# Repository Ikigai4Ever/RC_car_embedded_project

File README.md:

# RC_car_embedded_project

## PCB Portion 

- [NUCLEO-L476RG Footprints](https://www.snapeda.com/parts/NUCLEO-L476RG/STMicroelectronics/view-part/)
- [HC-05 Data Sheet](https://engineering.purdue.edu/477grp14/Team/journal/img%20-%20member3/documents/HC05.pdf)
- [Joystick Data Sheet](https://naylampmechatronics.com/img/cms/Datasheets/000036%20-%20datasheet%20KY-023-Joy-IT.pdf)

---

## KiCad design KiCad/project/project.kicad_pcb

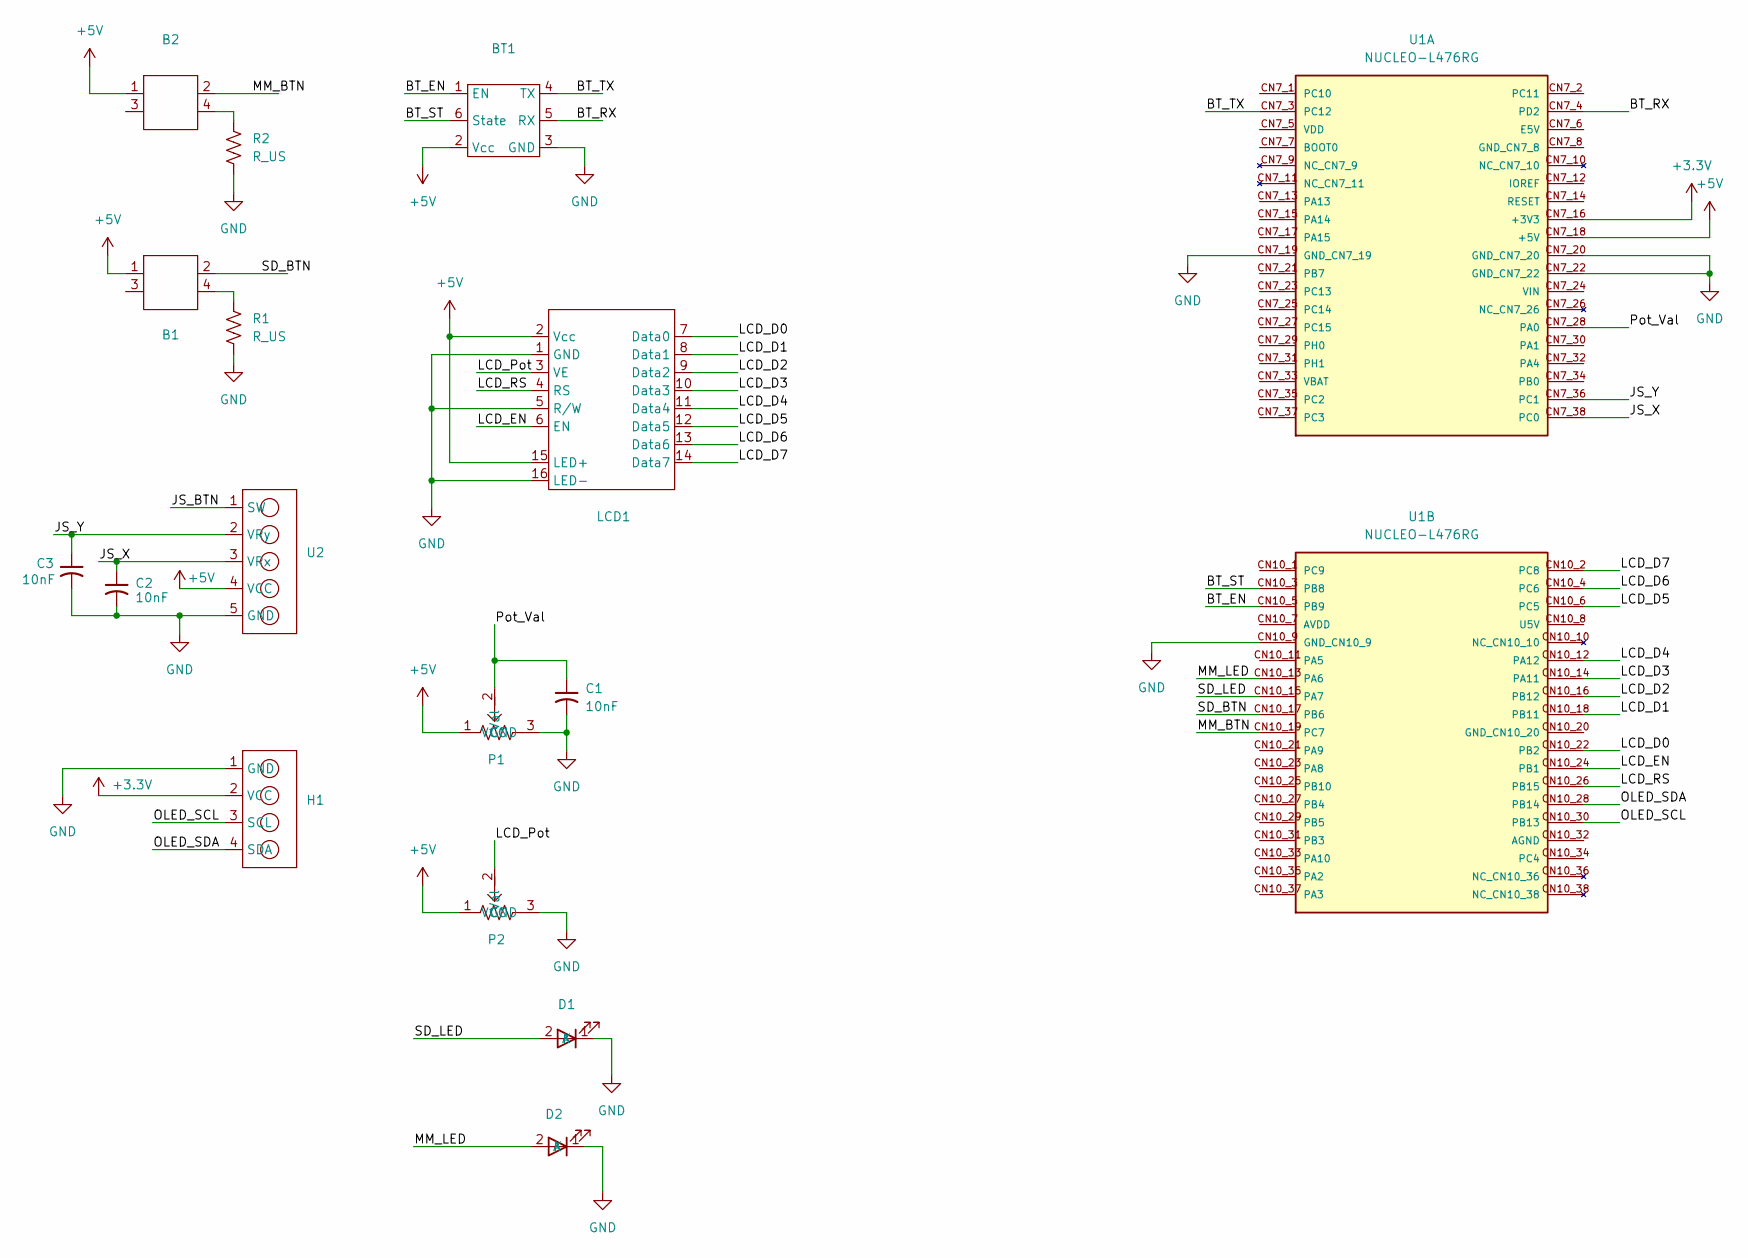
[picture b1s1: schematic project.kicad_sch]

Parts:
B1, B2: Button
BT1: HC-05
C1, C2, C3: 10nF; CAPC340180_88N_KEM
D1, D2: LED_THRU
H1: OLED
LCD1: LCD_Display
P1, P2: Potentiometer
R1, R2: R_US; RESC3216X65
U1: NUCLEO-L476RG; MODULE_NUCLEO-L476RG; PARTREV 15
U2: Joystick_Pins

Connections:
+3.3V: H1.2 (VCC), U1.CN7_16 (+3V3)
+5V: B1.1, B2.1, BT1.2 (Vcc), LCD1.2 (Vcc), LCD1.15 (LED+), P1.1 (VCC), P2.1 (VCC), U1.CN7_18 (+5V), U2.4 (VCC)
/BT_EN: BT1.1 (EN), U1.CN10_5 (PB9)
/BT_RX: BT1.5 (RX), U1.CN7_4 (PD2)
/BT_ST: BT1.6 (State), U1.CN10_3 (PB8)
/BT_TX: BT1.4 (TX), U1.CN7_3 (PC12)
/JS_BTN: U2.1 (SW)
/JS_X: C2.1, U1.CN7_38 (PC0), U2.3 (VRx)
/JS_Y: C3.1, U1.CN7_36 (PC1), U2.2 (VRy)
/LCD_D0: LCD1.7 (Data0), U1.CN10_22 (PB2)
/LCD_D1: LCD1.8 (Data1), U1.CN10_18 (PB11)
/LCD_D2: LCD1.9 (Data2), U1.CN10_16 (PB12)
/LCD_D3: LCD1.10 (Data3), U1.CN10_14 (PA11)
/LCD_D4: LCD1.11 (Data4), U1.CN10_12 (PA12)
/LCD_D5: LCD1.12 (Data5), U1.CN10_6 (PC5)
/LCD_D6: LCD1.13 (Data6), U1.CN10_4 (PC6)
/LCD_D7: LCD1.14 (Data7), U1.CN10_2 (PC8)
/LCD_EN: LCD1.6 (EN), U1.CN10_24 (PB1)
/LCD_Pot: LCD1.3 (VE), P2.2 (Val)
/LCD_RS: LCD1.4 (RS), U1.CN10_26 (PB15)
/MM_BTN: B2.2, U1.CN10_19 (PC7)
/MM_LED: D2.2 (A), U1.CN10_13 (PA6)
/OLED_SCL: H1.3 (SCL), U1.CN10_30 (PB13)
/OLED_SDA: H1.4 (SDA), U1.CN10_28 (PB14)
/Pot_Val: C1.1, P1.2 (Val), U1.CN7_28 (PA0)
/SD_BTN: B1.2, U1.CN10_17 (PB6)
/SD_LED: D1.2 (A), U1.CN10_15 (PA7)
GND: BT1.3 (GND), C1.2, C2.2, C3.2, D1.1 (K), D2.1 (K), H1.1 (GND), LCD1.1 (GND), LCD1.5 (R/W), LCD1.16 (LED-), P1.3 (GND), P2.3 (GND), R1.2, R2.2, U1.CN7_19 (GND_CN7_19), U1.CN7_20 (GND_CN7_20), U1.CN7_22 (GND_CN7_22), U1.CN10_9 (GND_CN10_9), U2.5 (GND)
unnamed: B1.4, R1.1
unnamed: B2.4, R2.1

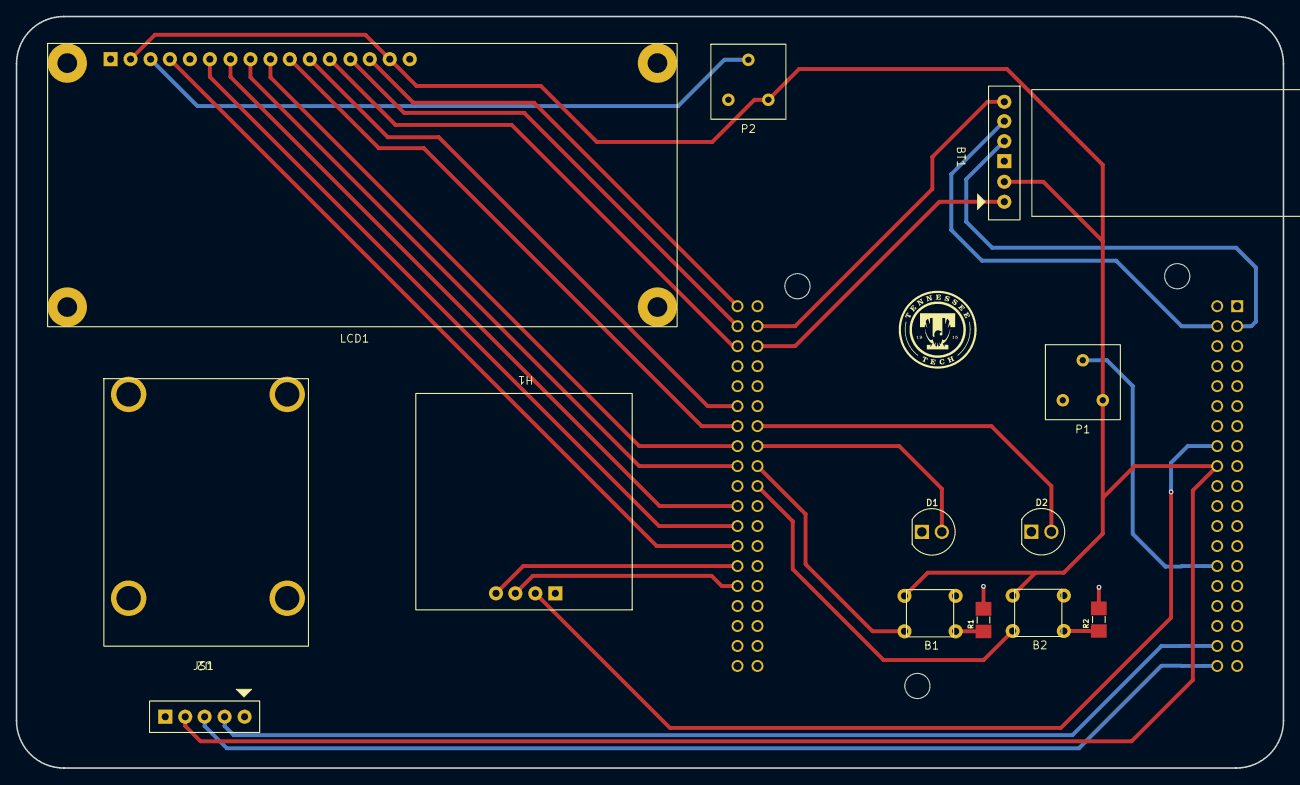
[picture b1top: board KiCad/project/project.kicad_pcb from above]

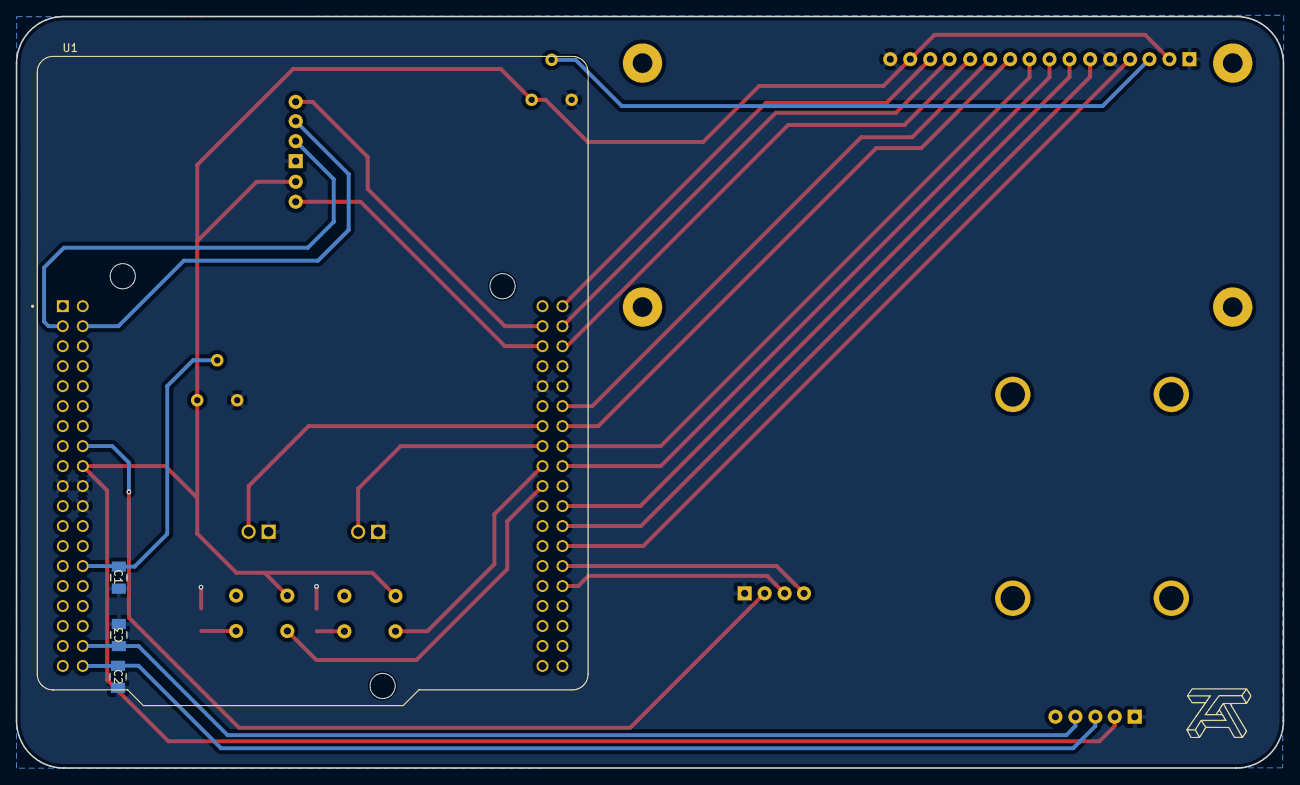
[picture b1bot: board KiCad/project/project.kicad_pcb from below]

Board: 2 copper layers, 161.0 x 95.5 mm, 17 parts (4 on the bottom side), 29 nets.

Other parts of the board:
JS1: Joystick

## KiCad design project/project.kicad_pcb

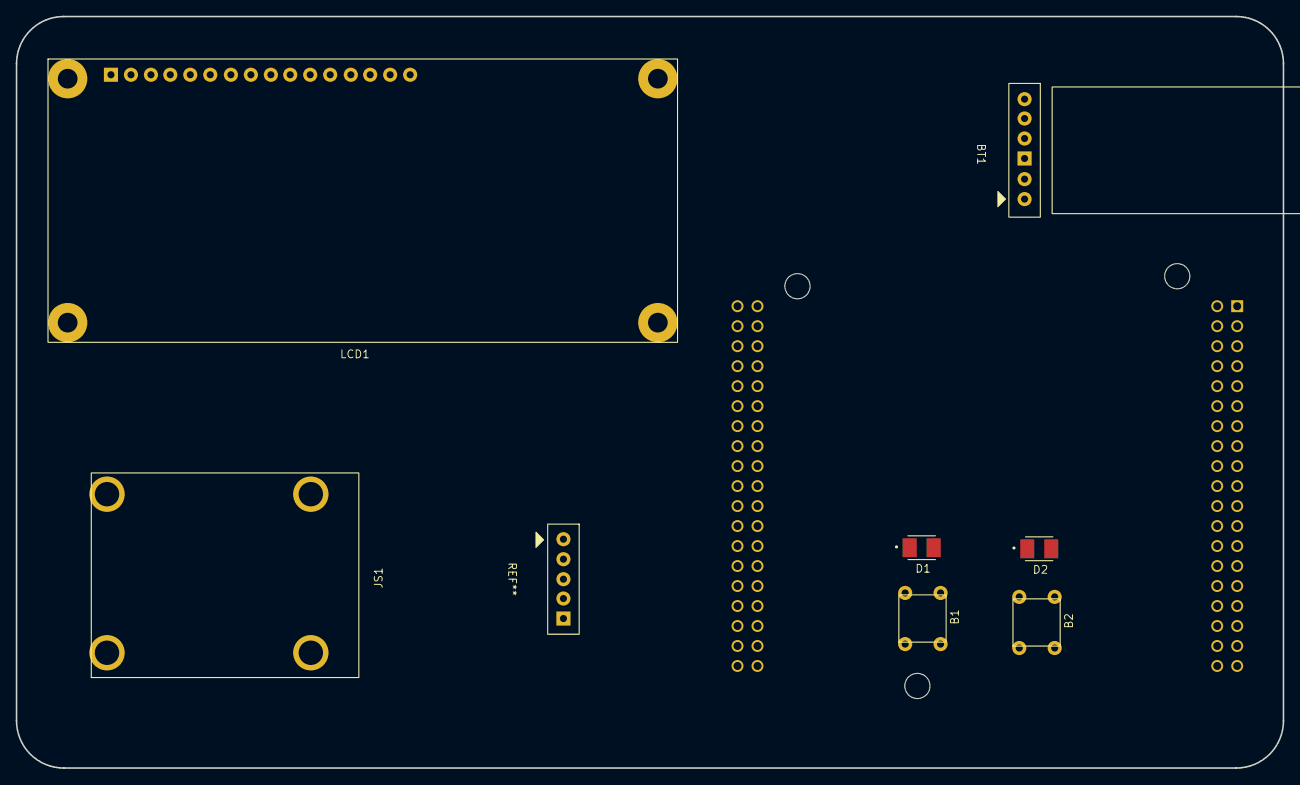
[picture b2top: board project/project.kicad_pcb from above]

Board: 2 copper layers, 161.0 x 95.5 mm, 8 parts (1 on the bottom side), 3 nets, no tracks yet.

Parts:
B1, B2: Button
BT1: HC-05
D1, D2: LED
JS1: Joystick
LCD1: LCD_Display
U1: NUCLEO-L476RG; MODULE_NUCLEO-L476RG

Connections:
GND: D1.1 (K), D2.1 (K)
unnamed: B1.4, D1.2 (A)
unnamed: B2.4, D2.2 (A)

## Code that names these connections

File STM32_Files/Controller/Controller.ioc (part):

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Mcu.Name=STM32L476R(C-E-G)Tx
Mcu.Package=LQFP64
Mcu.UserName=STM32L476RGTx
PA0.GPIOParameters=GPIO_Label
PA0.GPIO_Label=Pot_Val
PA0.Signal=ADCx_IN5
PA11.GPIOParameters=GPIO_Label
PA11.GPIO_Label=LCD_D3
PA11.Signal=GPIO_Output
PA12.GPIOParameters=GPIO_Label
PA12.GPIO_Label=LCD_D4
PA12.Signal=GPIO_Output
PA6.GPIOParameters=GPIO_Label
PA6.GPIO_Label=Manual_Mode_LED
PA6.Signal=GPIO_Output
PA7.GPIOParameters=GPIO_Label
PA7.GPIO_Label=SD_Mode_LED
PA7.Signal=GPIO_Output
PB1.GPIOParameters=GPIO_Label
PB1.GPIO_Label=LCD_EN
PB1.Signal=GPIO_Output
PB11.GPIOParameters=GPIO_Label
PB11.GPIO_Label=LCD_D1
PB11.Signal=GPIO_Output
PB12.GPIOParameters=GPIO_Label
PB12.GPIO_Label=LCD_D2
PB12.Signal=GPIO_Output
PB13.GPIOParameters=GPIO_Label
PB13.GPIO_Label=OLED_SCL
PB13.Mode=I2C
PB13.Signal=I2C2_SCL
PB14.GPIOParameters=GPIO_Label
PB14.GPIO_Label=OLED_SDA
PB14.Mode=I2C
PB14.Signal=I2C2_SDA
PB15.GPIOParameters=GPIO_Label
PB15.GPIO_Label=LCD_RS
PB15.Signal=GPIO_Output
PB2.GPIOParameters=GPIO_Label
PB2.GPIO_Label=LCD_D0
PB2.Signal=GPIO_Output
PB6.GPIOParameters=GPIO_Label
PB6.GPIO_Label=SD_Button
PB6.Signal=GPIO_Output
PB8.GPIOParameters=GPIO_Label
PB8.GPIO_Label=Bluetooth_State
PB8.Signal=GPIO_Output
PB9.GPIOParameters=GPIO_Label
PB9.GPIO_Label=Bluetooth_Enable
PB9.Signal=GPIO_Output
PC0.GPIOParameters=GPIO_Label
PC0.GPIO_Label=JS_X
PC0.Signal=ADCx_IN1
PC1.GPIOParameters=GPIO_Label
PC1.GPIO_Label=JS_Y
PC1.Signal=ADCx_IN2
PC12.GPIOParameters=GPIO_Label
PC12.GPIO_Label=Bluetooth_TX
PC12.Mode=Asynchronous
PC12.Signal=UART5_TX
PC5.GPIOParameters=GPIO_Label
PC5.GPIO_Label=LCD_D5
PC5.Signal=GPIO_Output
PC6.GPIOParameters=GPIO_Label
PC6.GPIO_Label=LCD_D6
PC6.Signal=GPIO_Output
PC7.GPIOParameters=GPIO_Label
PC7.GPIO_Label=Manual_Mode_Button
PC7.Signal=GPIO_Input
PC8.GPIOParameters=GPIO_Label
PC8.GPIO_Label=LCD_D7
PC8.Signal=GPIO_Output
PD2.GPIOParameters=GPIO_Label
PD2.GPIO_Label=Bluetooth_RX
PD2.Mode=Asynchronous
PD2.Signal=UART5_RX
RCC.HSE_VALUE=8000000
RCC.SYSCLKFreq_VALUE=80000000
RCC.SYSCLKSource=RCC_SYSCLKSOURCE_PLLCLK
board=NUCLEO-L476RG
boardIOC=true

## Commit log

2025-10-20 Update README with PCB section and resources
    Added PCB portion with relevant links.
2025-10-20 Added in both libraries
    Added in both footprint libraries for the schematic and the pcb design
2025-10-20 Added project file
    Added in the project file as well to view on own device
2025-10-20 Updated project & create pinout map
    Updated the project file and added another footprint library that needs to be added. Also created a .ioc file for the controller STM32
2025-10-20 Added pin map for controller
2025-10-22 Added BOM for Project
    Added a good chunk of materials for the Seeker module, still need to think about servos, fuses, capacitors, and different wire AWGS
2025-10-28 Add Nucleo pinout image to README
    Added image of Nucleo pinout to README.
2025-10-29 Updated PCB schematic and pinout for the ioc file because it was funky
2025-10-29 Updated pinnout for controller
2025-10-31 Update stuff :)
2025-11-02 Updated schematic to get ready to send out
2025-11-03 Updated .ioc file for the controller
2025-11-08 Updated PCB for parallel capacitors
2025-11-17 Created the test_motor folder
    This folder contains the code for the motor testing before wireless communication. Inside are the Main.c and IOC file.
2025-11-17 Added the Motor_Test ioc file
2025-11-21 Uploaded Controller Project
2025-11-21 Create README.md for Bluetooth STM32 project
    Added comprehensive README.md for Bluetooth STM32 project, detailing setup, features, and usage instructions.
2025-11-21 Revise README for Bluetooth UART STM32 Library
    Updated README to clarify Bluetooth library functionality and corrected baud rate information.
2025-11-21 Added in bluetooth send/receive functionality
2025-11-22 Change baud rate in Bluetooth UART STM32 README
    Updated baud rate from 115200 to 9600 in README.
2025-11-22 Moving files to correct places
2025-11-22 Create RC_Car_Seeker
2025-11-22 Added Seeker files
2025-11-22 Wrong folder, should be STM32_Files
2025-11-22 Added seeker main file in repo
2025-11-22 added seeker ioc file
2025-11-22 Added Project Report
2025-11-23 Uploading updated code for controller
2025-11-23 Hopefully this works :)
2025-11-24 Added in 3D models for pcb
2025-11-24 FInished up 3D model for the STM32 Board
2025-11-24 Uploaded PCB Pictures w/ 3D models
2025-11-28 Deleted This version of Seeker IOC to change it
2025-11-28 Updated Seeker IOC
2025-11-28 Updated Seeker main.c
2025-12-02 I LOVE COLLEGE
2025-12-02 Moving FIles
2025-12-02 Added README.md
2025-12-02 Uploaded Controller ZIP
